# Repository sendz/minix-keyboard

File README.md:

# STILL IN PROGRESS!

# MINIX

## A 50% Keyboard that fits 104 keysets

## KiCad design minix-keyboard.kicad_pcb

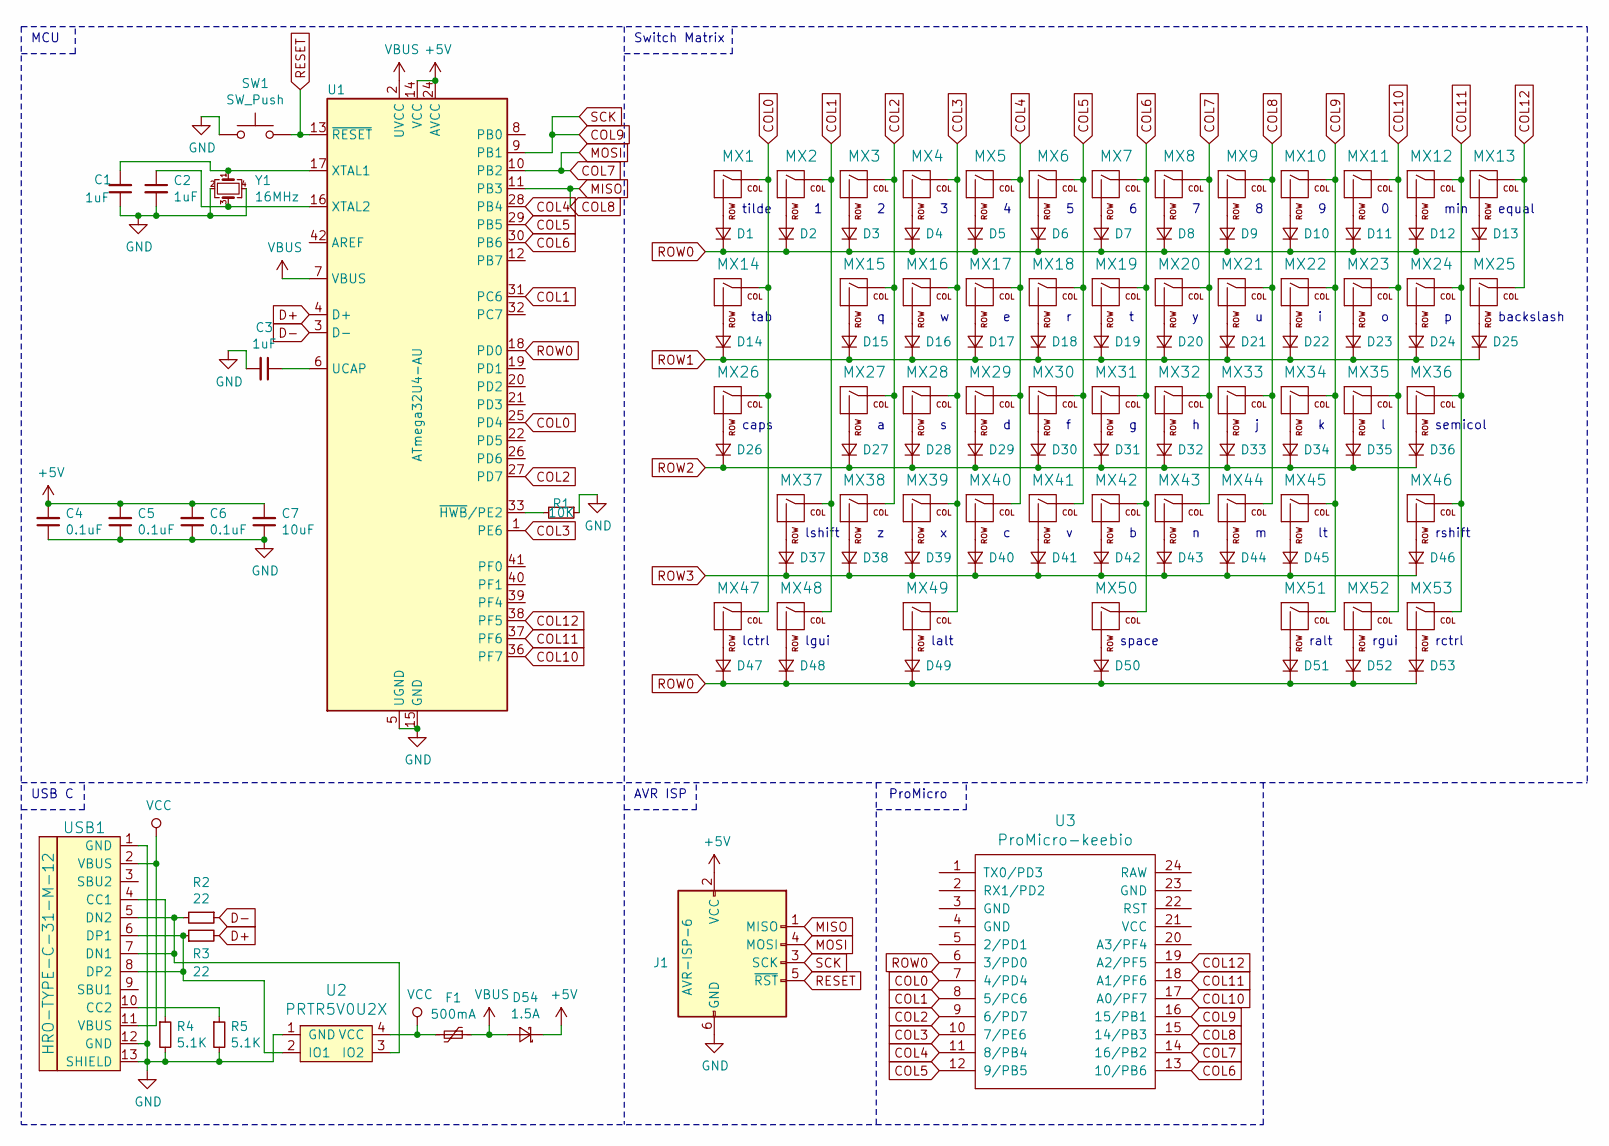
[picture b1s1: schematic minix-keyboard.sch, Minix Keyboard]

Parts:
C1, C2, C3: 1uF; C_0805_2012Metric
C4, C5, C6: 0.1uF; C_0805_2012Metric
C7: 10uF; C_0805_2012Metric
D1, D2, D3, D4, D5, D6, D7, D8, D9, D10, D11, D12, D13, D14, D15, D16, D17, D18, D19, D20, D21, D22, D23, D24, D25, D26, D27, D28, D29, D30, D31, D32, D33, D34, D35, D36, D37, D38, D39, D40, D41, D42, D43, D44, D45, D46, D47, D48, D49, D50, D51, D52, D53: 1N4148; D_SOD-123
D54: 1.5A; D_SOD-123F
F1: 500mA; Fuse_1206_3216Metric
J1: AVR-ISP-6; PinHeader_2x03_P2.54mm_Vertical
MX1, MX2, MX3, MX4, MX5, MX6, MX7, MX8, MX9, MX10, MX11, MX12, MX13, MX15, MX16, MX17, MX18, MX19, MX20, MX21, MX22, MX23, MX24, MX27, MX28, MX29, MX30, MX31, MX32, MX33, MX34, MX35, MX38, MX39, MX40, MX41, MX42, MX43, MX44, MX45, MX51, MX52, MX53: MX-NoLED; MXOnly-1U-NoLED
MX14, MX25: MX-NoLED; MXOnly-1.5U-NoLED
MX26: MX-NoLED; MXOnly-1.75U-NoLED
MX36, MX37: MX-NoLED; MXOnly-2.25U-NoLED
MX46: MX-NoLED; MXOnly-2.75U-NoLED
MX47, MX48, MX49: MX-NoLED; MXOnly-1.25U-NoLED
MX50: MX-NoLED; MXOnly-6.25U-ReversedStabilizers-NoLED
R1: 10K; R_0805_2012Metric
R2, R3: 22; R_0805_2012Metric
R4, R5: 5.1K; R_0805_2012Metric
SW1: SW_Push; SW_SPST_TL3342
U1: ATmega32U4-AU; TQFP-44_10x10mm_P0.8mm
U2: PRTR5V0U2X; SOT-143
U3: ProMicro-keebio; ArduinoProMicro-TopSide
USB1: HRO-TYPE-C-31-M-12
Y1: 16MHz; Crystal_SMD_3225-4Pin_3.2x2.5mm

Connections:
+5V: C4.2, C5.2, C6.2, C7.2, D54.1 (K), J1.2 (VCC), U1.14 (VCC), U1.24 (AVCC), U1.34 (VCC), U1.44 (AVCC)
COL0: MX1.1 (COL), MX14.1 (COL), MX26.1 (COL), MX47.1 (COL), U1.25 (PD4), U3.7 (4/PD4)
COL1: MX2.1 (COL), MX37.1 (COL), MX48.1 (COL), U1.31 (PC6), U3.8 (5/PC6)
COL2: MX3.1 (COL), MX15.1 (COL), MX27.1 (COL), MX38.1 (COL), U1.27 (PD7), U3.9 (6/PD7)
COL3: MX4.1 (COL), MX16.1 (COL), MX28.1 (COL), MX39.1 (COL), MX49.1 (COL), U1.1 (PE6), U3.10 (7/PE6)
COL4: MX5.1 (COL), MX17.1 (COL), MX29.1 (COL), MX40.1 (COL), U1.28 (PB4), U3.11 (8/PB4)
COL5: MX6.1 (COL), MX18.1 (COL), MX30.1 (COL), MX41.1 (COL), U1.29 (PB5), U3.12 (9/PB5)
COL6: MX7.1 (COL), MX19.1 (COL), MX31.1 (COL), MX42.1 (COL), MX50.1 (COL), U1.30 (PB6), U3.13 (10/PB6)
COL7: J1.4 (MOSI), MX8.1 (COL), MX20.1 (COL), MX32.1 (COL), MX43.1 (COL), U1.10 (PB2), U3.14 (16/PB2)
COL8: J1.1 (MISO), MX9.1 (COL), MX21.1 (COL), MX33.1 (COL), MX44.1 (COL), U1.11 (PB3), U3.15 (14/PB3)
COL9: J1.3 (SCK), MX10.1 (COL), MX22.1 (COL), MX34.1 (COL), MX45.1 (COL), MX51.1 (COL), U1.9 (PB1), U3.16 (15/PB1)
COL10: MX11.1 (COL), MX23.1 (COL), MX35.1 (COL), MX52.1 (COL), U1.36 (PF7), U3.17 (A0/PF7)
COL11: MX12.1 (COL), MX24.1 (COL), MX36.1 (COL), MX46.1 (COL), MX53.1 (COL), U1.37 (PF6), U3.18 (A1/PF6)
COL12: MX13.1 (COL), MX25.1 (COL), U1.38 (PF5), U3.19 (A2/PF5)
D+: R3.2, U1.4 (D+)
D-: R2.1, U1.3 (D-)
GND: C1.1, C2.2, C3.2, C4.1, C5.1, C6.1, C7.1, J1.6 (GND), R1.1, R4.2, R5.2, SW1.1, U1.5 (UGND), U1.15 (GND), U1.23 (GND), U1.35 (GND), U1.43 (GND), U2.1 (GND), USB1.1 (GND), USB1.12 (GND), USB1.13 (SHIELD), Y1.2, Y1.4
unnamed: C1.2, U1.17 (XTAL1), Y1.1
unnamed: C2.1, U1.16 (XTAL2), Y1.3
unnamed: C3.1, U1.6 (UCAP)
unnamed: D1.2 (A), MX1.2 (ROW)
unnamed: D2.2 (A), MX2.2 (ROW)
unnamed: D3.2 (A), MX3.2 (ROW)
unnamed: D4.2 (A), MX4.2 (ROW)
unnamed: D5.2 (A), MX5.2 (ROW)
unnamed: D6.2 (A), MX6.2 (ROW)
unnamed: D7.2 (A), MX7.2 (ROW)
unnamed: D8.2 (A), MX8.2 (ROW)
unnamed: D9.2 (A), MX9.2 (ROW)
unnamed: D10.2 (A), MX10.2 (ROW)
unnamed: D11.2 (A), MX11.2 (ROW)
unnamed: D12.2 (A), MX12.2 (ROW)
unnamed: D13.2 (A), MX13.2 (ROW)
unnamed: D14.2 (A), MX14.2 (ROW)
unnamed: D15.2 (A), MX15.2 (ROW)
unnamed: D16.2 (A), MX16.2 (ROW)
unnamed: D17.2 (A), MX17.2 (ROW)
unnamed: D18.2 (A), MX18.2 (ROW)
unnamed: D19.2 (A), MX19.2 (ROW)
unnamed: D20.2 (A), MX20.2 (ROW)
unnamed: D21.2 (A), MX21.2 (ROW)
unnamed: D22.2 (A), MX22.2 (ROW)
unnamed: D23.2 (A), MX23.2 (ROW)
unnamed: D24.2 (A), MX24.2 (ROW)
unnamed: D25.2 (A), MX25.2 (ROW)
unnamed: D26.2 (A), MX26.2 (ROW)
unnamed: D27.2 (A), MX27.2 (ROW)
unnamed: D28.2 (A), MX28.2 (ROW)
unnamed: D29.2 (A), MX29.2 (ROW)
unnamed: D30.2 (A), MX30.2 (ROW)
unnamed: D31.2 (A), MX31.2 (ROW)
unnamed: D32.2 (A), MX32.2 (ROW)
unnamed: D33.2 (A), MX33.2 (ROW)
unnamed: D34.2 (A), MX34.2 (ROW)
unnamed: D35.2 (A), MX35.2 (ROW)
unnamed: D36.2 (A), MX36.2 (ROW)
unnamed: D37.2 (A), MX37.2 (ROW)
unnamed: D38.2 (A), MX38.2 (ROW)
unnamed: D39.2 (A), MX39.2 (ROW)
unnamed: D40.2 (A), MX40.2 (ROW)
unnamed: D41.2 (A), MX41.2 (ROW)
unnamed: D42.2 (A), MX42.2 (ROW)
unnamed: D43.2 (A), MX43.2 (ROW)
unnamed: D44.2 (A), MX44.2 (ROW)
unnamed: D45.2 (A), MX45.2 (ROW)
unnamed: D46.2 (A), MX46.2 (ROW)
unnamed: D47.2 (A), MX47.2 (ROW)
unnamed: D48.2 (A), MX48.2 (ROW)
unnamed: D49.2 (A), MX49.2 (ROW)
unnamed: D50.2 (A), MX50.2 (ROW)
unnamed: D51.2 (A), MX51.2 (ROW)
unnamed: D52.2 (A), MX52.2 (ROW)
unnamed: D53.2 (A), MX53.2 (ROW)
unnamed: R1.2, U1.33 (~HWB~/PE2)
unnamed: R2.2, U2.3 (IO2), USB1.5 (DN2), USB1.7 (DN1)
unnamed: R3.1, U2.2 (IO1), USB1.6 (DP1), USB1.8 (DP2)
unnamed: R4.1, USB1.4 (CC1)
unnamed: R5.1, USB1.10 (CC2)
RESET: J1.5 (~RST), SW1.2, U1.13 (~RESET)
ROW0: D1.1 (K), D2.1 (K), D3.1 (K), D4.1 (K), D5.1 (K), D6.1 (K), D7.1 (K), D8.1 (K), D9.1 (K), D10.1 (K), D11.1 (K), D12.1 (K), D13.1 (K), D47.1 (K), D48.1 (K), D49.1 (K), D50.1 (K), D51.1 (K), D52.1 (K), D53.1 (K), U1.18 (PD0), U3.6 (3/PD0)
ROW1: D14.1 (K), D15.1 (K), D16.1 (K), D17.1 (K), D18.1 (K), D19.1 (K), D20.1 (K), D21.1 (K), D22.1 (K), D23.1 (K), D24.1 (K), D25.1 (K)
ROW2: D26.1 (K), D27.1 (K), D28.1 (K), D29.1 (K), D30.1 (K), D31.1 (K), D32.1 (K), D33.1 (K), D34.1 (K), D35.1 (K), D36.1 (K)
ROW3: D37.1 (K), D38.1 (K), D39.1 (K), D40.1 (K), D41.1 (K), D42.1 (K), D43.1 (K), D44.1 (K), D45.1 (K), D46.1 (K)
VBUS: D54.2 (A), F1.1, U1.2 (UVCC), U1.7 (VBUS)
VCC: F1.2, U2.4 (VCC), USB1.2 (VBUS), USB1.11 (VBUS)

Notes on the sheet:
tilde
min
equal
tab
backslash
caps
semicol
lshift
rshift
lctrl
lgui
lalt
space
ralt
rgui
rctrl
MCU
Switch Matrix
AVR ISP
USB C
ProMicro

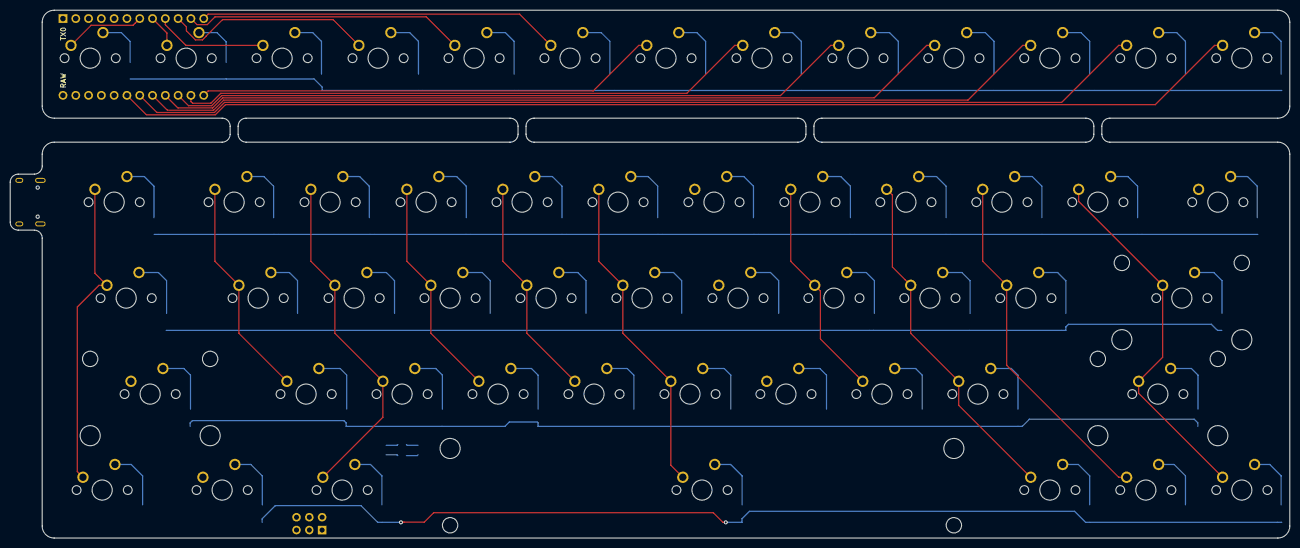
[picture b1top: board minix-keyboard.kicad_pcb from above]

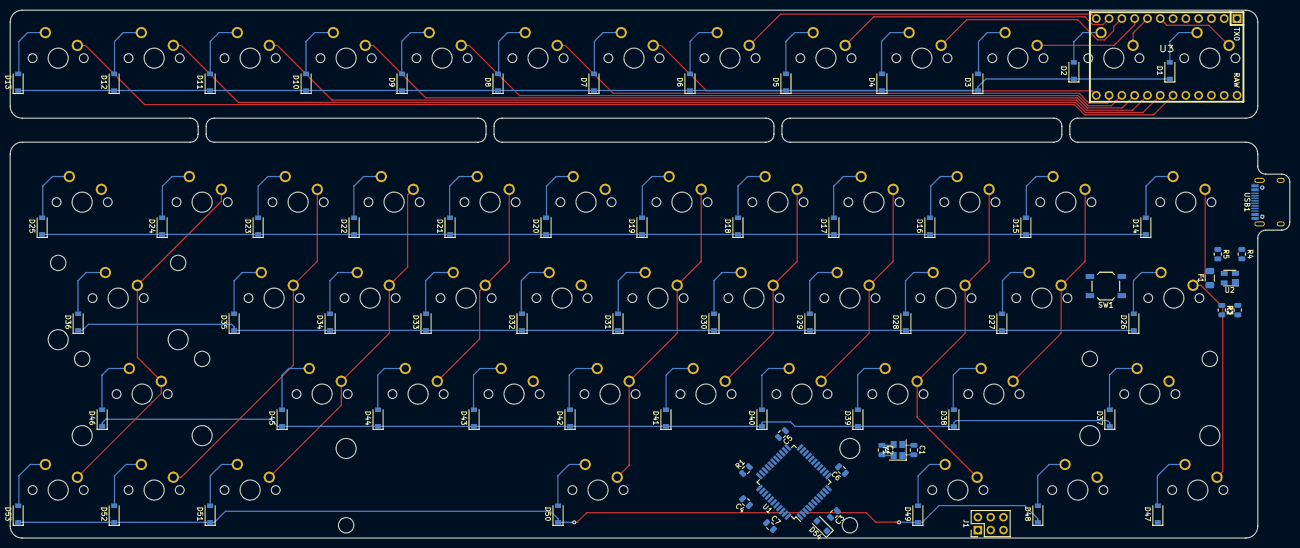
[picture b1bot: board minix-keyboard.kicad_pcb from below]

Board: 2 copper layers, 254.0 x 104.8 mm, 127 parts (74 on the bottom side), 85 nets.

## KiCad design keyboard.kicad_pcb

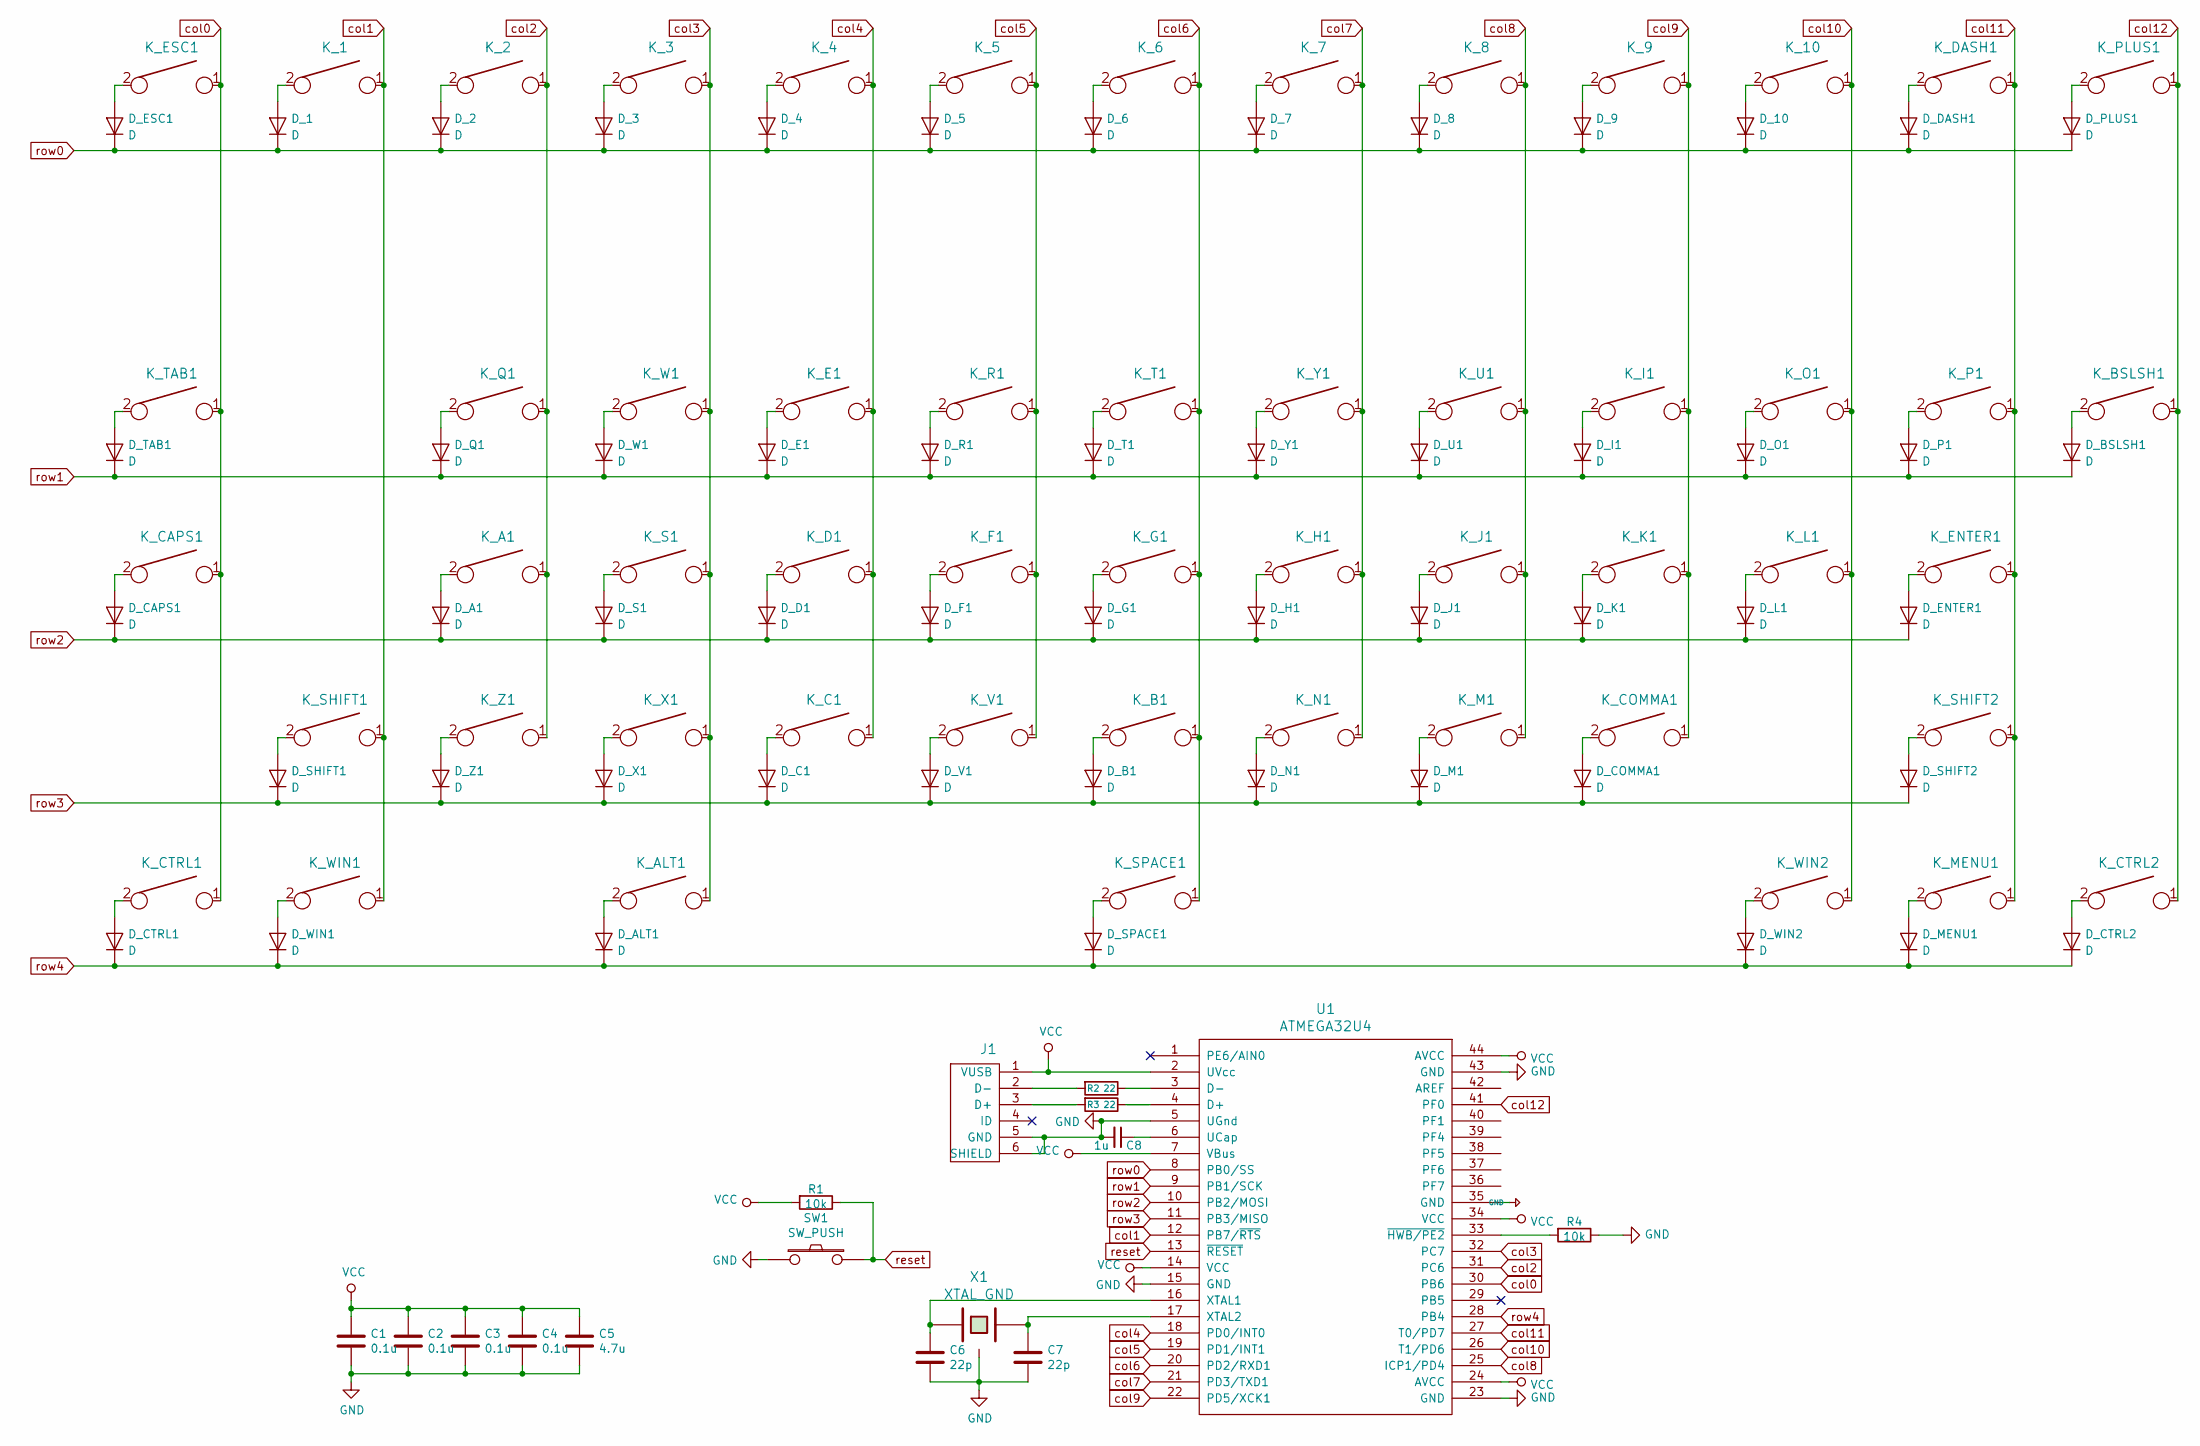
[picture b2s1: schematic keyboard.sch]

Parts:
C1, C2, C3, C4: 0.1u; C_0805_2012Metric_Pad1.15x1.40mm_HandSolder
C5: 4.7u; C_0805_2012Metric_Pad1.15x1.40mm_HandSolder
C6, C7: 22p; C_0805_2012Metric_Pad1.15x1.40mm_HandSolder
C8: 1u; C_0805_2012Metric_Pad1.15x1.40mm_HandSolder
D_1, D_2, D_3, D_4, D_5, D_6, D_7, D_8, D_9, D_10: D; D_SOD123_axial
D_A1: D; D_SOD123_axial
D_ALT1: D; D_SOD123_axial
D_B1: D; D_SOD123_axial
D_BSLSH1: D; D_SOD123_axial
D_C1: D; D_SOD123_axial
D_CAPS1: D; D_SOD123_axial
D_COMMA1: D; D_SOD123_axial
D_CTRL1, D_CTRL2: D; D_SOD123_axial
D_D1: D; D_SOD123_axial
D_DASH1: D; D_SOD123_axial
D_E1: D; D_SOD123_axial
D_ENTER1: D; D_SOD123_axial
D_ESC1: D; D_SOD123_axial
D_F1: D; D_SOD123_axial
D_G1: D; D_SOD123_axial
D_H1: D; D_SOD123_axial
D_I1: D; D_SOD123_axial
D_J1: D; D_SOD123_axial
D_K1: D; D_SOD123_axial
D_L1: D; D_SOD123_axial
D_M1: D; D_SOD123_axial
D_MENU1: D; D_SOD123_axial
D_N1: D; D_SOD123_axial
D_O1: D; D_SOD123_axial
D_P1: D; D_SOD123_axial
D_PLUS1: D; D_SOD123_axial
D_Q1: D; D_SOD123_axial
D_R1: D; D_SOD123_axial
D_S1: D; D_SOD123_axial
D_SHIFT1, D_SHIFT2: D; D_SOD123_axial
D_SPACE1: D; D_SOD123_axial
D_T1: D; D_SOD123_axial
D_TAB1: D; D_SOD123_axial
D_U1: D; D_SOD123_axial
D_V1: D; D_SOD123_axial
D_W1: D; D_SOD123_axial
D_WIN1, D_WIN2: D; D_SOD123_axial
D_X1: D; D_SOD123_axial
D_Y1: D; D_SOD123_axial
D_Z1: D; D_SOD123_axial
J1: USB_mini_micro_B; USB-Mini-B_ LCSC-C46398
K_1, K_2, K_3, K_4, K_5, K_6, K_7, K_8, K_9, K_10: KEYSW; MX-1U-NoLED
K_A1: KEYSW; MX-1U-NoLED
K_ALT1: KEYSW; MX-1.25U-NoLED
K_B1: KEYSW; MX-1U-NoLED
K_BSLSH1: KEYSW; MX-1.5U-NoLED
K_C1: KEYSW; MX-1U-NoLED
K_CAPS1: KEYSW; MX-1.75U-NoLED
K_COMMA1: KEYSW; MX-1U-NoLED
K_CTRL1: KEYSW; MX-1.25U-NoLED
K_CTRL2: KEYSW; MX-1U-NoLED
K_D1: KEYSW; MX-1U-NoLED
K_DASH1: KEYSW; MX-1U-NoLED
K_E1: KEYSW; MX-1U-NoLED
K_ENTER1: KEYSW; MX-2.25U-NoLED
K_ESC1: KEYSW; MX-1U-NoLED
K_F1: KEYSW; MX-1U-NoLED
K_G1: KEYSW; MX-1U-NoLED
K_H1: KEYSW; MX-1U-NoLED
K_I1: KEYSW; MX-1U-NoLED
K_J1: KEYSW; MX-1U-NoLED
K_K1: KEYSW; MX-1U-NoLED
K_L1: KEYSW; MX-1U-NoLED
K_M1: KEYSW; MX-1U-NoLED
K_MENU1: KEYSW; MX-1U-NoLED
K_N1: KEYSW; MX-1U-NoLED
K_O1: KEYSW; MX-1U-NoLED
K_P1: KEYSW; MX-1U-NoLED
K_PLUS1: KEYSW; MX-1U-NoLED
K_Q1: KEYSW; MX-1U-NoLED
K_R1: KEYSW; MX-1U-NoLED
K_S1: KEYSW; MX-1U-NoLED
K_SHIFT1: KEYSW; MX-2.25U-NoLED
K_SHIFT2: KEYSW; MX-2.75U-NoLED
K_SPACE1: KEYSW; MX-6.25U-NoLED
K_T1: KEYSW; MX-1U-NoLED
K_TAB1: KEYSW; MX-1.5U-NoLED
K_U1: KEYSW; MX-1U-NoLED
K_V1: KEYSW; MX-1U-NoLED
K_W1: KEYSW; MX-1U-NoLED
K_WIN1: KEYSW; MX-1.25U-NoLED
K_WIN2: KEYSW; MX-1U-NoLED
K_X1: KEYSW; MX-1U-NoLED
K_Y1: KEYSW; MX-1U-NoLED
K_Z1: KEYSW; MX-1U-NoLED
R1, R4: 10k; R_0805_2012Metric_Pad1.15x1.40mm_HandSolder
R2, R3: 22; R_0805_2012Metric_Pad1.15x1.40mm_HandSolder
SW1: SW_PUSH; SW_SPST_TL3342
U1: ATMEGA32U4; TQFP-44_10x10mm_P0.8mm
X1: XTAL_GND; Crystal_SMD_3225-4pin_3.2x2.5mm

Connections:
unnamed: C6.1, U1.16 (XTAL1), X1.1
unnamed: C7.1, U1.17 (XTAL2), X1.2
unnamed: C8.1, U1.6 (UCap)
unnamed: D_1.2 (A), K_1.2
unnamed: D_2.2 (A), K_2.2
unnamed: D_3.2 (A), K_3.2
unnamed: D_4.2 (A), K_4.2
unnamed: D_5.2 (A), K_5.2
unnamed: D_6.2 (A), K_6.2
unnamed: D_7.2 (A), K_7.2
unnamed: D_8.2 (A), K_8.2
unnamed: D_9.2 (A), K_9.2
unnamed: D_10.2 (A), K_10.2
unnamed: D_A1.2 (A), K_A1.2
unnamed: D_ALT1.2 (A), K_ALT1.2
unnamed: D_B1.2 (A), K_B1.2
unnamed: D_BSLSH1.2 (A), K_BSLSH1.2
unnamed: D_C1.2 (A), K_C1.2
unnamed: D_CAPS1.2 (A), K_CAPS1.2
unnamed: D_COMMA1.2 (A), K_COMMA1.2
unnamed: D_CTRL1.2 (A), K_CTRL1.2
unnamed: D_CTRL2.2 (A), K_CTRL2.2
unnamed: D_D1.2 (A), K_D1.2
unnamed: D_DASH1.2 (A), K_DASH1.2
unnamed: D_E1.2 (A), K_E1.2
unnamed: D_ENTER1.2 (A), K_ENTER1.2
unnamed: D_ESC1.2 (A), K_ESC1.2
unnamed: D_F1.2 (A), K_F1.2
unnamed: D_G1.2 (A), K_G1.2
unnamed: D_H1.2 (A), K_H1.2
unnamed: D_I1.2 (A), K_I1.2
unnamed: D_J1.2 (A), K_J1.2
unnamed: D_K1.2 (A), K_K1.2
unnamed: D_L1.2 (A), K_L1.2
unnamed: D_M1.2 (A), K_M1.2
unnamed: D_MENU1.2 (A), K_MENU1.2
unnamed: D_N1.2 (A), K_N1.2
unnamed: D_O1.2 (A), K_O1.2
unnamed: D_P1.2 (A), K_P1.2
unnamed: D_PLUS1.2 (A), K_PLUS1.2
unnamed: D_Q1.2 (A), K_Q1.2
unnamed: D_R1.2 (A), K_R1.2
unnamed: D_S1.2 (A), K_S1.2
unnamed: D_SHIFT1.2 (A), K_SHIFT1.2
unnamed: D_SHIFT2.2 (A), K_SHIFT2.2
unnamed: D_SPACE1.2 (A), K_SPACE1.2
unnamed: D_T1.2 (A), K_T1.2
unnamed: D_TAB1.2 (A), K_TAB1.2
unnamed: D_U1.2 (A), K_U1.2
unnamed: D_V1.2 (A), K_V1.2
unnamed: D_W1.2 (A), K_W1.2
unnamed: D_WIN1.2 (A), K_WIN1.2
unnamed: D_WIN2.2 (A), K_WIN2.2
unnamed: D_X1.2 (A), K_X1.2
unnamed: D_Y1.2 (A), K_Y1.2
unnamed: D_Z1.2 (A), K_Z1.2
unnamed: J1.2 (D-), R2.2
unnamed: J1.3 (D+), R3.2
unnamed: R2.1, U1.3 (D-)
unnamed: R3.1, U1.4 (D+)
unnamed: R4.2, U1.33 (~HWB/PE2)
VCC: C1.1, C2.1, C3.1, C4.1, C5.1, J1.1 (VUSB), R1.2, U1.2 (UVcc), U1.7 (VBus), U1.14 (VCC), U1.24 (AVCC), U1.34 (VCC), U1.44 (AVCC)
col0: K_CAPS1.1, K_CTRL1.1, K_ESC1.1, K_TAB1.1, U1.30 (PB6)
col1: K_1.1, K_SHIFT1.1, K_WIN1.1, U1.12 (PB7/~RTS)
col2: K_2.1, K_A1.1, K_Q1.1, K_Z1.1, U1.31 (PC6)
col3: K_3.1, K_ALT1.1, K_S1.1, K_W1.1, K_X1.1, U1.32 (PC7)
col4: K_4.1, K_C1.1, K_D1.1, K_E1.1, U1.18 (PD0/INT0)
col5: K_5.1, K_F1.1, K_R1.1, K_V1.1, U1.19 (PD1/INT1)
col6: K_6.1, K_B1.1, K_G1.1, K_SPACE1.1, K_T1.1, U1.20 (PD2/RXD1)
col7: K_7.1, K_H1.1, K_N1.1, K_Y1.1, U1.21 (PD3/TXD1)
col8: K_8.1, K_J1.1, K_M1.1, K_U1.1, U1.25 (ICP1/PD4)
col9: K_9.1, K_COMMA1.1, K_I1.1, K_K1.1, U1.22 (PD5/XCK1)
col10: K_10.1, K_L1.1, K_O1.1, K_WIN2.1, U1.26 (T1/PD6)
col11: K_DASH1.1, K_ENTER1.1, K_MENU1.1, K_P1.1, K_SHIFT2.1, U1.27 (T0/PD7)
col12: K_BSLSH1.1, K_CTRL2.1, K_PLUS1.1, U1.41 (PF0)
reset: R1.1, SW1.2, U1.13 (~RESET)
row0: D_1.1 (K), D_2.1 (K), D_3.1 (K), D_4.1 (K), D_5.1 (K), D_6.1 (K), D_7.1 (K), D_8.1 (K), D_9.1 (K), D_10.1 (K), D_DASH1.1 (K), D_ESC1.1 (K), D_PLUS1.1 (K), U1.8 (PB0/SS)
row1: D_BSLSH1.1 (K), D_E1.1 (K), D_I1.1 (K), D_O1.1 (K), D_P1.1 (K), D_Q1.1 (K), D_R1.1 (K), D_T1.1 (K), D_TAB1.1 (K), D_U1.1 (K), D_W1.1 (K), D_Y1.1 (K), U1.9 (PB1/SCK)
row2: D_A1.1 (K), D_CAPS1.1 (K), D_D1.1 (K), D_ENTER1.1 (K), D_F1.1 (K), D_G1.1 (K), D_H1.1 (K), D_J1.1 (K), D_K1.1 (K), D_L1.1 (K), D_S1.1 (K), U1.10 (PB2/MOSI)
row3: D_B1.1 (K), D_C1.1 (K), D_COMMA1.1 (K), D_M1.1 (K), D_N1.1 (K), D_SHIFT1.1 (K), D_SHIFT2.1 (K), D_V1.1 (K), D_X1.1 (K), D_Z1.1 (K), U1.11 (PB3/MISO)
row4: D_ALT1.1 (K), D_CTRL1.1 (K), D_CTRL2.1 (K), D_MENU1.1 (K), D_SPACE1.1 (K), D_WIN1.1 (K), D_WIN2.1 (K), U1.28 (PB4)

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
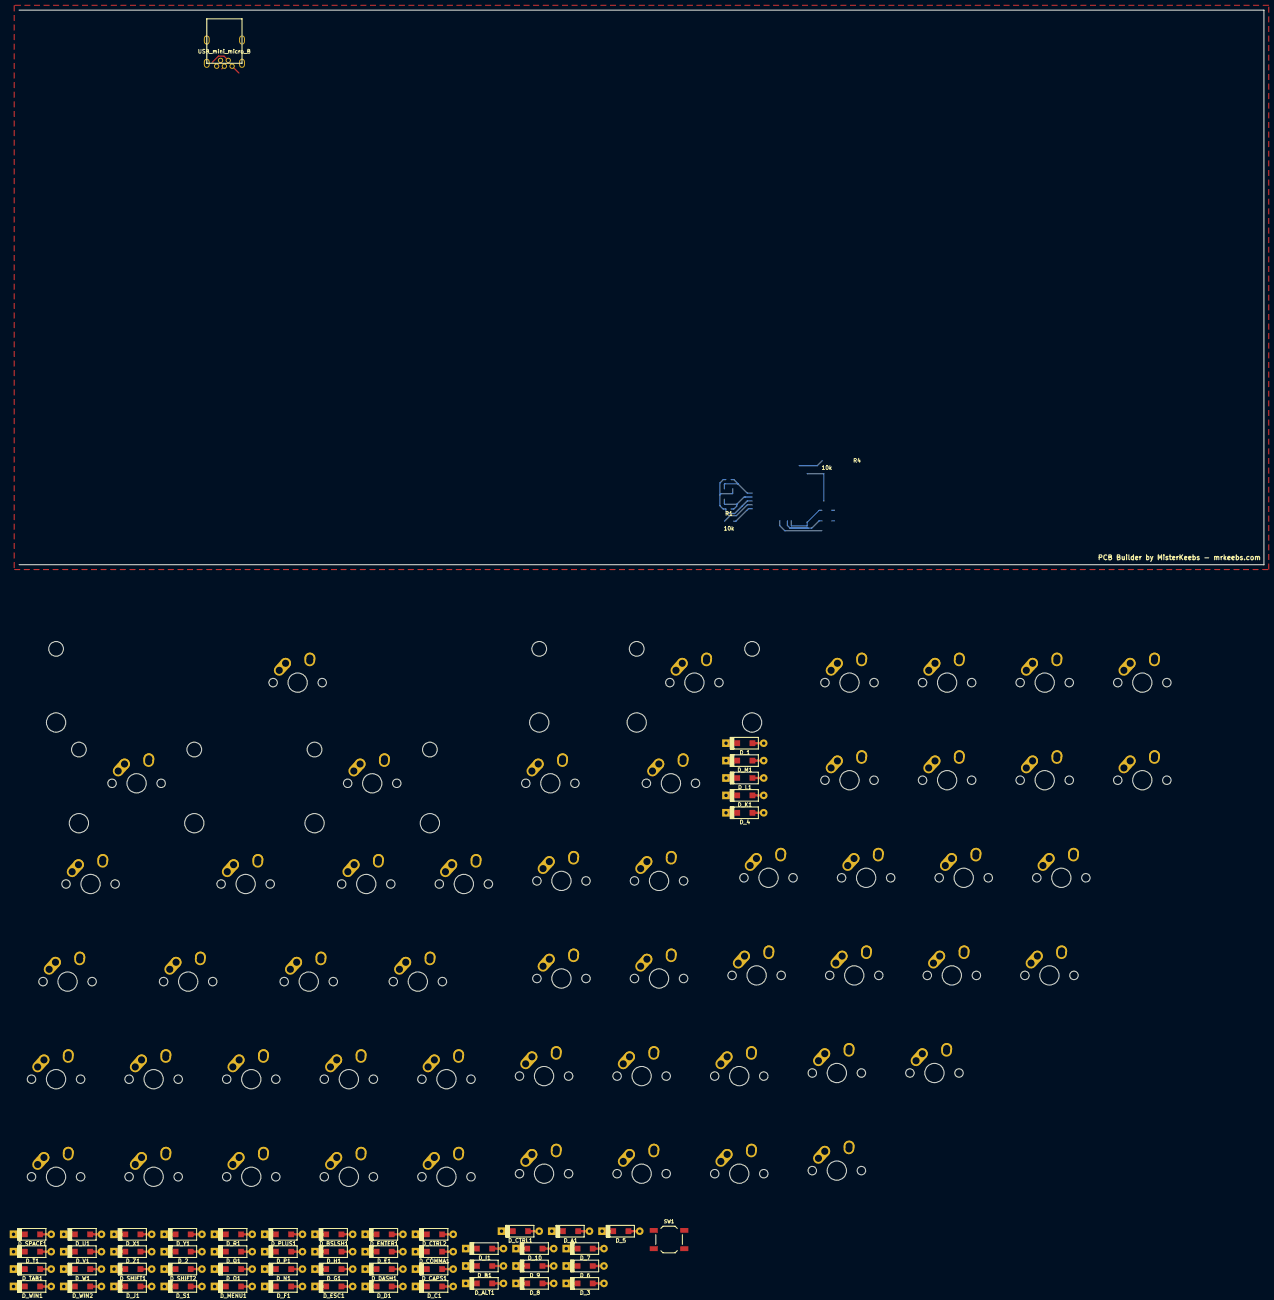
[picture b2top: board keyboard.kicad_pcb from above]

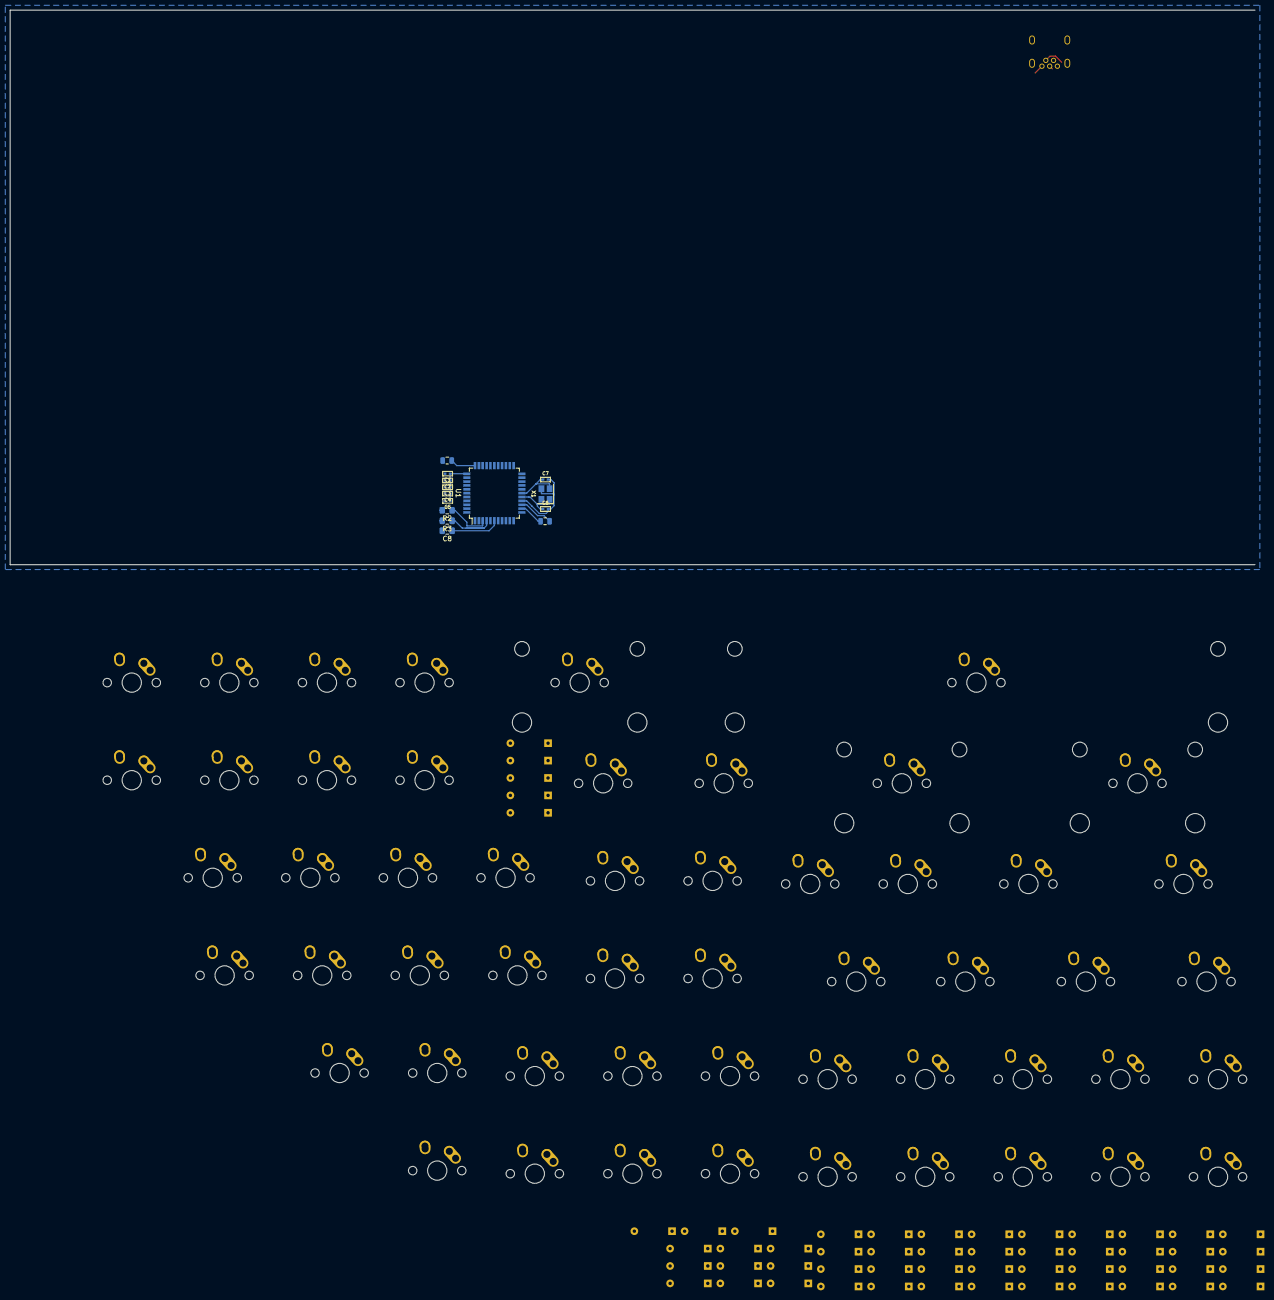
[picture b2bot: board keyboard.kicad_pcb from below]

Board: 2 copper layers, 257.6 x 114.8 mm, 122 parts (14 on the bottom side), 82 nets.

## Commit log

2020-08-28 Add readme
2020-08-28 Add note
2020-08-30 re-init kicad project
2020-09-15 Add promicro header
2020-09-15 Update schematic
2020-09-15 Routing switches
